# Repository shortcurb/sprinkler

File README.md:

# sprinkler
For controlling my house sprinklers with a Raspberry Pi and a custom PCB

mqttclient.service handles the MQTT listening for commands and sending responses
sprinklerer.service handles the GPIO pin changing to control different relays
scheduler.service handles checking for weather and sunrise/sunset (solar) data

sprinklerer interacts with other modules purely through redis/celery
I needed an abstraction layer that has exclusive control over the GPIOs to prevent all manner of negative effects with the sprinklers including:
* More than one zone turning on at a time
* Turning more than one zone off at a time (water hammer possible)
* Thinking I turned all the relays/zones off, but then some dormant zombie process coming back and turning one/more back on
* Some other process crashing and leaving the zones turned on forever

scheduler handles 

mqttclient is the only other module that interacts via redis/celery, just adding and cancelling sprinkling and stopping tasks

scheduler handles 

To Do:
* Pull any sensitive info out and put it in a .env and .gitignore it
* Rethink the queuing system. I have no visibility into the Celery thing
    * Maybe there's a way I can handle a queue within python? Have the scheduler spin up a process and do it? Something with async?

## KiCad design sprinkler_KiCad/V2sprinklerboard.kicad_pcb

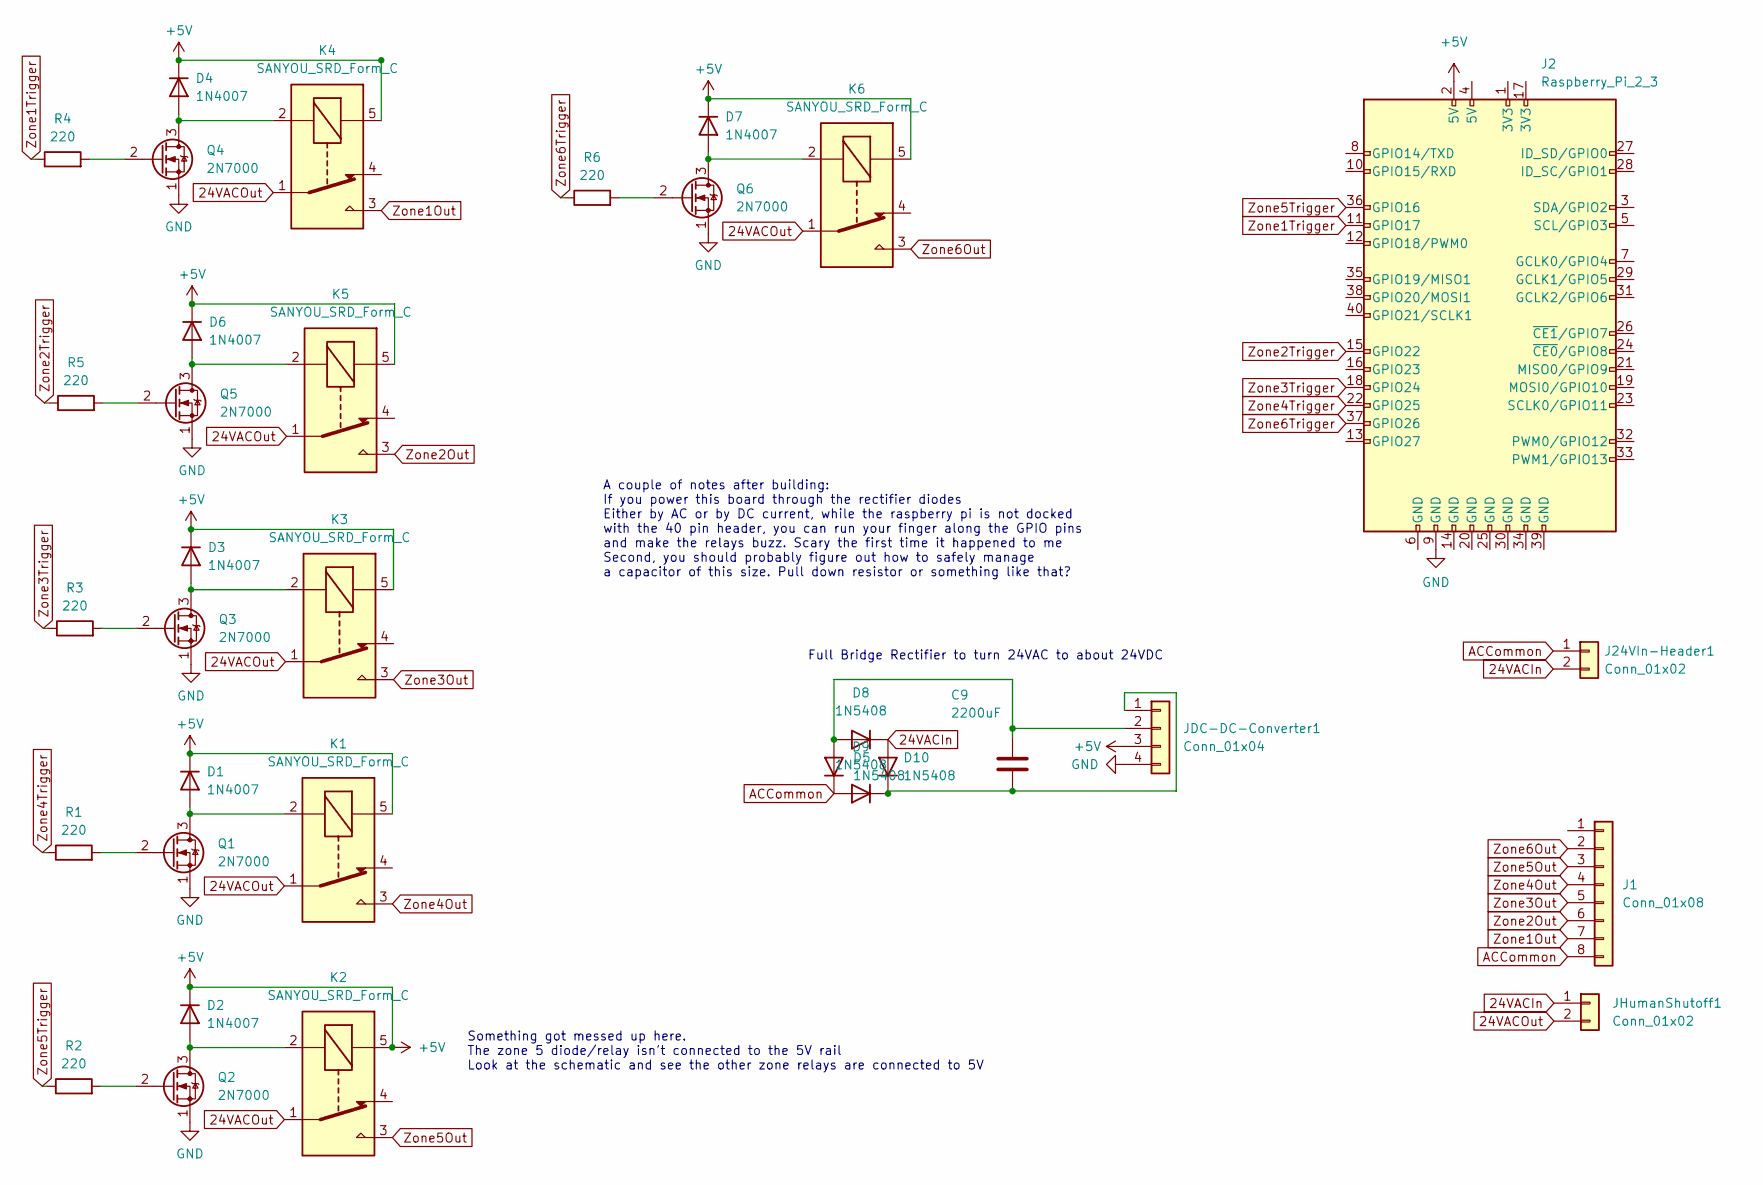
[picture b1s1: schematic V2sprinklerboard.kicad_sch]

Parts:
C9: 2200uF; C_Radial_D16.0mm_H25.0mm_P7.50mm
D1, D2, D3, D4, D6, D7: 1N4007; D_DO-41_SOD81_P10.16mm_Horizontal
D5, D8, D9, D10: 1N5408; D_DO-201AD_P15.24mm_Horizontal
J1: Conn_01x08; TerminalBlock_Phoenix_MKDS-1,5-8_1x08_P5.00mm_Horizontal
J2: Raspberry_Pi_2_3; RPi Full size -AE
J24VIn-Header1: Conn_01x02; TerminalBlock_Phoenix_MKDS-1,5-2_1x02_P5.00mm_Horizontal
JDC-DC-Converter1: Conn_01x04; XL6009E1 DC-DC
JHumanShutoff1: Conn_01x02; JST_EH_B2B-EH-A_1x02_P2.50mm_Vertical
K1, K2, K3, K4, K5, K6: SANYOU_SRD_Form_C; Relay_SPDT_SANYOU_SRD_Series_Form_C
Q1, Q2, Q3, Q4, Q5, Q6: 2N7000; TO-92_Inline
R1, R2, R3, R4, R5, R6: 220; R_Axial_DIN0411_L9.9mm_D3.6mm_P12.70mm_Horizontal

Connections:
24VACIn: D8.1 (K), D10.2 (A), J24VIn-Header1.2, JHumanShutoff1.1
24VACOut: JHumanShutoff1.2, K1.1, K2.1, K3.1, K4.1, K5.1, K6.1
+5V: D1.1 (K), D3.1 (K), D4.1 (K), D6.1 (K), D7.1 (K), J2.2 (5V), JDC-DC-Converter1.3, K1.5, K3.5, K4.5, K5.5, K6.5
ACCommon: D5.1 (K), D9.2 (A), J1.8 (INT), J24VIn-Header1.1
GND: J2.9 (GND), JDC-DC-Converter1.4, Q1.1 (S), Q2.1 (S), Q3.1 (S), Q4.1 (S), Q5.1 (S), Q6.1 (S)
unnamed: C9.1, D5.2 (A), D8.2 (A), JDC-DC-Converter1.2
unnamed: C9.2, D9.1 (K), D10.1 (K), JDC-DC-Converter1.1
unnamed: D1.2 (A), K1.2, Q1.3 (D)
unnamed: D2.1 (K), K2.5
unnamed: D2.2 (A), K2.2, Q2.3 (D)
unnamed: D3.2 (A), K3.2, Q3.3 (D)
unnamed: D4.2 (A), K4.2, Q4.3 (D)
unnamed: D6.2 (A), K5.2, Q5.3 (D)
unnamed: D7.2 (A), K6.2, Q6.3 (D)
unnamed: Q1.2 (G), R1.2
unnamed: Q2.2 (G), R2.2
unnamed: Q3.2 (G), R3.2
unnamed: Q4.2 (G), R4.2
unnamed: Q5.2 (G), R5.2
unnamed: Q6.2 (G), R6.2
Zone1Out: J1.7 (AD0), K4.3
Zone1Trigger: J2.11 (GPIO17), R4.1
Zone2Out: J1.6 (XDA), K5.3
Zone2Trigger: J2.15 (GPIO22), R5.1
Zone3Out: J1.5 (XCL), K3.3
Zone3Trigger: J2.18 (GPIO24), R3.1
Zone4Out: J1.4 (SDA), K1.3
Zone4Trigger: J2.22 (GPIO25), R1.1
Zone5Out: J1.3 (SCL), K2.3
Zone5Trigger: J2.36 (GPIO16), R2.1
Zone6Out: J1.2 (Pin2), K6.3
Zone6Trigger: J2.37 (GPIO26), R6.1

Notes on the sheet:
A couple of notes after building: If you power this board through the rectifier diodes Either by AC or by DC current, while the raspberry pi is not docked with the 40 pin header, you can run your finger along the GPIO pins and make the relays buzz. Scary the first time it happened to me Second, you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
Something got messed up here. The zone 5 diode/relay isn't connected to the 5V rail Look at the schematic and see the other zone relays are connected to 5V
Full Bridge Rectifier to turn 24VAC to about 24VDC

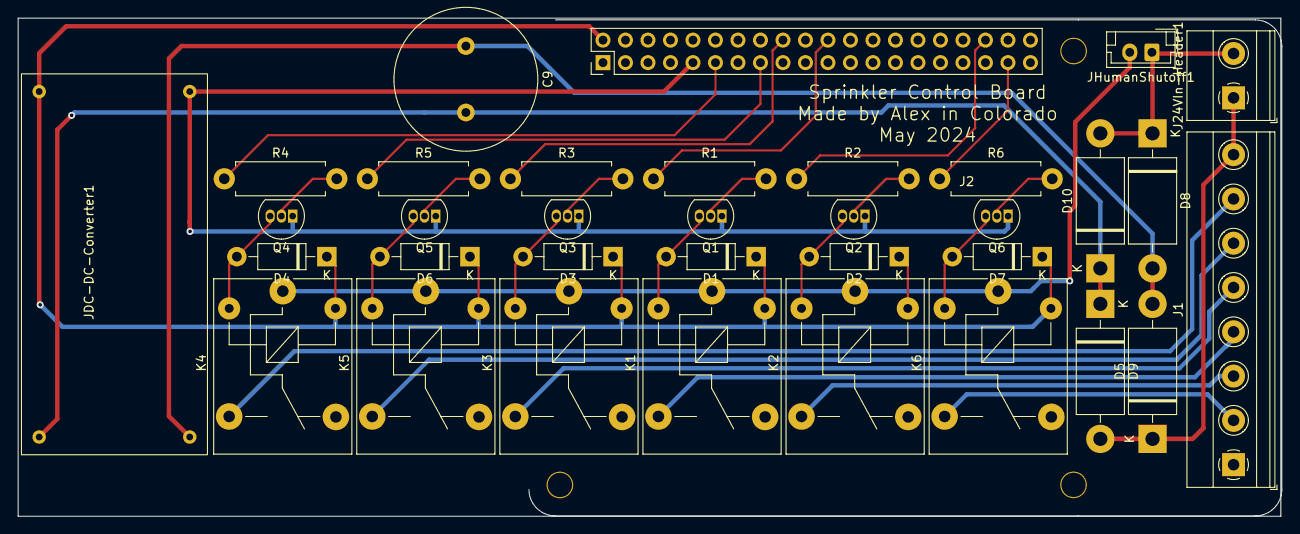
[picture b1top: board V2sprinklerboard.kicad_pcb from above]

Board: 2 copper layers, 142.7 x 56.2 mm, 34 parts (0 on the bottom side), 32 nets.

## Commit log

2024-08-17 working
2024-08-17 working with HA
2024-08-21 rewrite without celery
2025-03-28 update
    might be some duplicates
2025-05-09 bugfixes
2025-05-12 cleaned up folder structure
2025-05-12 bug fix
2025-05-12 added 3d printable case
2025-05-12 added ttl
2025-06-11 fix circular import
